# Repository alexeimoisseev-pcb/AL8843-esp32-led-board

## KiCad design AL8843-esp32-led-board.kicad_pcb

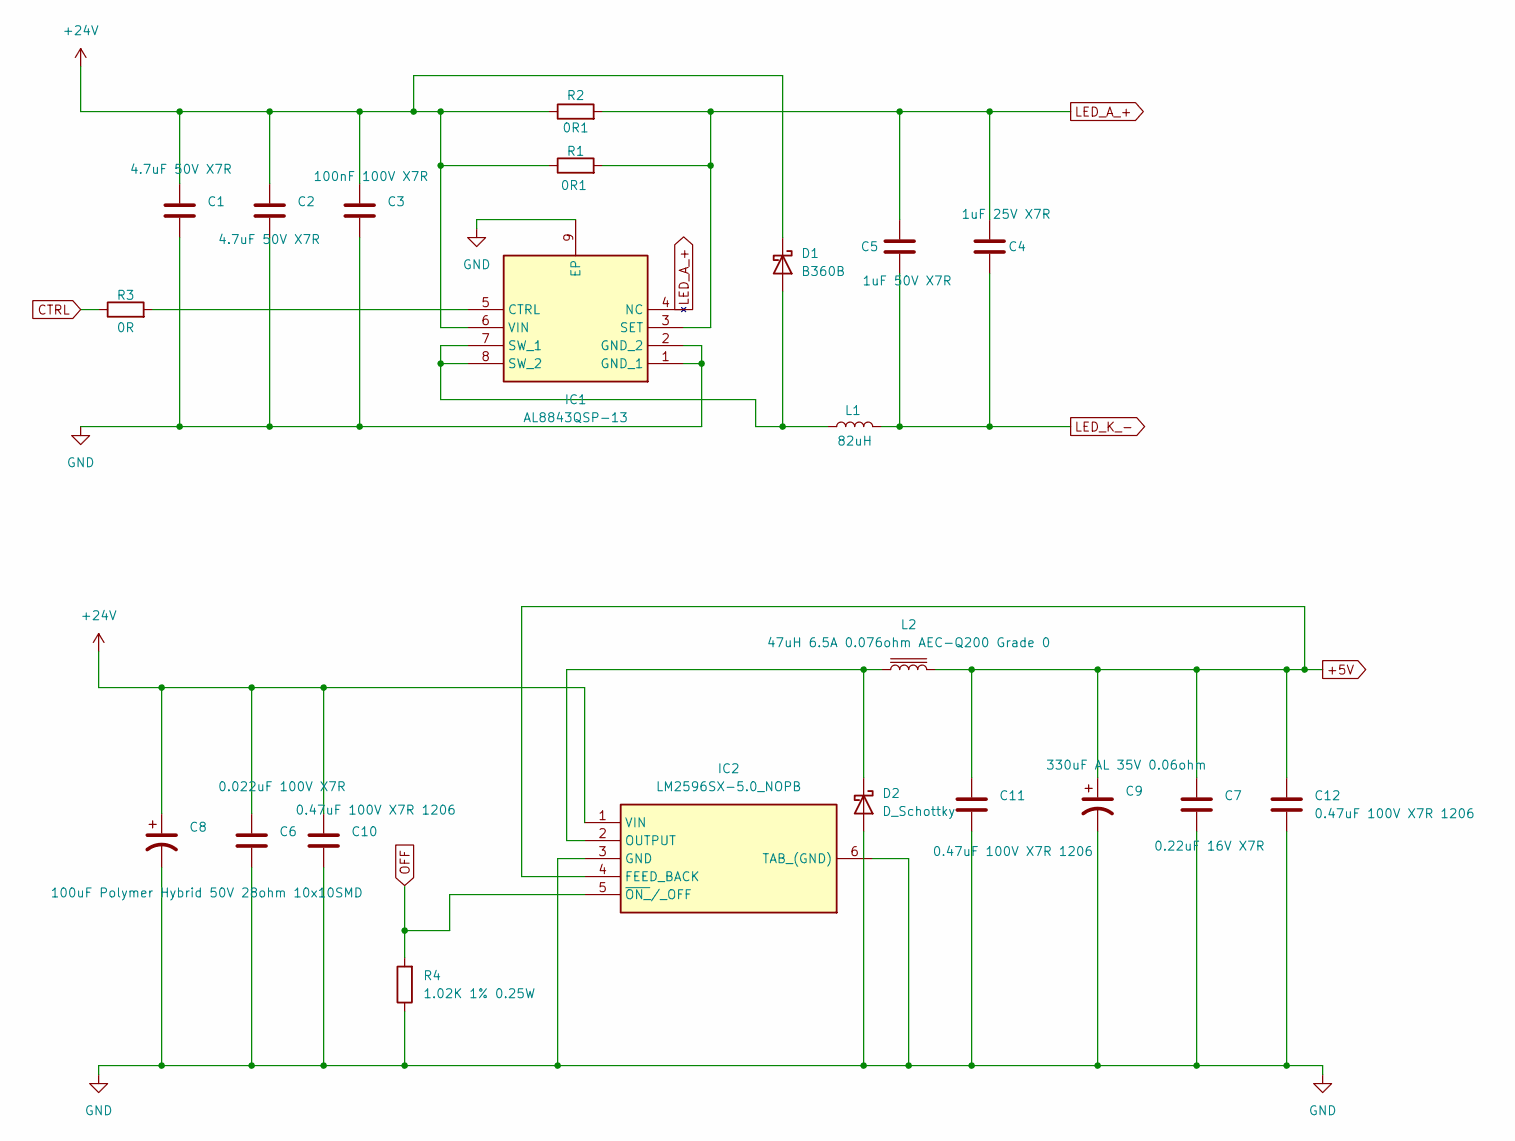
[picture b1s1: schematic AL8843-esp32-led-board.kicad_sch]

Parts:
C1, C2: 4.7uF 50V X7R; C_1206_3216Metric; LCSC C51205
C3: 100nF 100V X7R; C_0805_2012Metric; LCSC C28233
C4: 1uF 25V X7R; C_0603_1608Metric; LCSC C29936
C5: 1uF 50V X7R; C_0603_1608Metric; LCSC C5199872
C6: 0.022uF 100V X7R; C_0603_1608Metric; LCSC C472763
C7: 0.22uF 16V X7R; C_0402_1005Metric; LCSC C16772
C8: 100uF Polymer Hybrid 50V 28ohm 10x10SMD; C_Elec_10x10.2; LCSC C161937
C9: 330uF AL 35V 0.06ohm; CP_Elec_8x10; LCSC C178598
C10, C11, C12: 0.47uF 100V X7R 1206; C_1206_3216Metric; LCSC C472853
D1: B360B; D_SMB; LCSC C91546
D2: D_Schottky; D_SMC; LCSC C134461
IC1: AL8843QSP-13; SOIC127P600X170-9N; Manufacturer_Part_Number AL8843QSP-13; Mouser Part Number 621-AL8843QSP-13
IC2: LM2596SX-5.0_NOPB; KTT0005B; Manufacturer_Part_Number LM2596SX-5.0/NOPB; Mouser Part Number 926-LM2596SX-5.0NOPB
L1: 82uH; L_12x12mm_H6mm; LCSC C7431084
L2: 47uH 6.5A 0.076ohm AEC-Q200 Grade 0; L_TechFuse_SL1265; LCSC C22463855
R1, R2: 0R1; R_2512_6332Metric; LCSC C419755
R3: 0R; R_1206_3216Metric; LCSC C17888
R4: 1.02K 1% 0.25W; R_1206_3216Metric; LCSC C488549

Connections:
+5V: C7.1, C9.1, C11.1, C12.1, IC2.4 (FEED_BACK), L2.2
+24V: C1.1, C2.1, C3.1, C6.1, C8.1, C10.1, D1.1 (K), IC1.6 (VIN), IC2.1 (VIN), R1.1, R2.1
CTRL: R3.1; also elsewhere on the board
GND: C1.2, C2.2, C3.2, C6.2, C7.2, C8.2, C9.2, C10.2, C11.2, C12.2, D2.2 (A), IC1.1 (GND_1), IC1.2 (GND_2), IC1.9 (EP), IC2.3 (GND), IC2.6 (TAB_(GND)), IC2.7, IC2.8, R4.1; also elsewhere on the board
LED_A_+: C4.1, C5.1, IC1.3 (SET), IC1.4 (NC), R1.2, R2.2
LED_K_-: C4.2, C5.2, L1.2
unnamed: D1.2 (A), IC1.7 (SW_1), IC1.8 (SW_2), L1.1
unnamed: D2.1 (K), IC2.2 (OUTPUT), L2.1
unnamed: IC1.5 (CTRL), R3.2
OFF: IC2.5 (~ON_/_OFF), R4.2; also elsewhere on the board

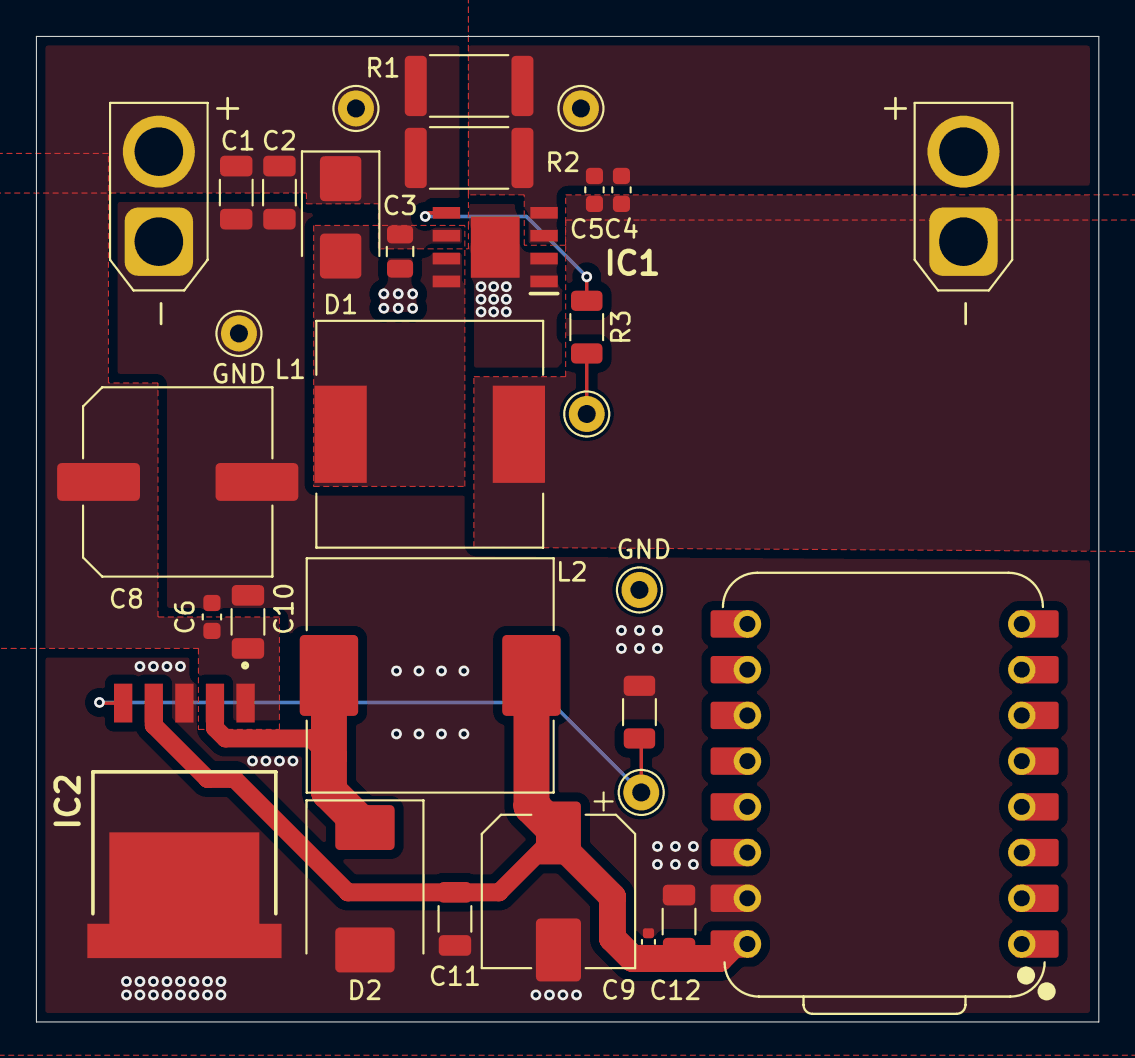
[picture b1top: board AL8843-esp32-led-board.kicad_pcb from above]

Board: 2 copper layers, 59.0 x 54.8 mm, 26 parts (0 on the bottom side), 10 nets.

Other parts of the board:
CTRL: Pin_D1.0mm_L10.0mm
GND: Pin_D1.0mm_L10.0mm
GND#2: Pin_D1.0mm_L10.0mm
OFF: Pin_D1.0mm_L10.0mm

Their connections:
CTRL: CTRL.1; also elsewhere on the board
GND: GND.1; also elsewhere on the board
OFF: OFF.1; also elsewhere on the board

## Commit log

2025-08-12 AL8843-esp32-led-board initial version
2025-08-12 jlcpcb order W2025081219518153
2025-08-14 ESP32 power
2025-08-19 misc
